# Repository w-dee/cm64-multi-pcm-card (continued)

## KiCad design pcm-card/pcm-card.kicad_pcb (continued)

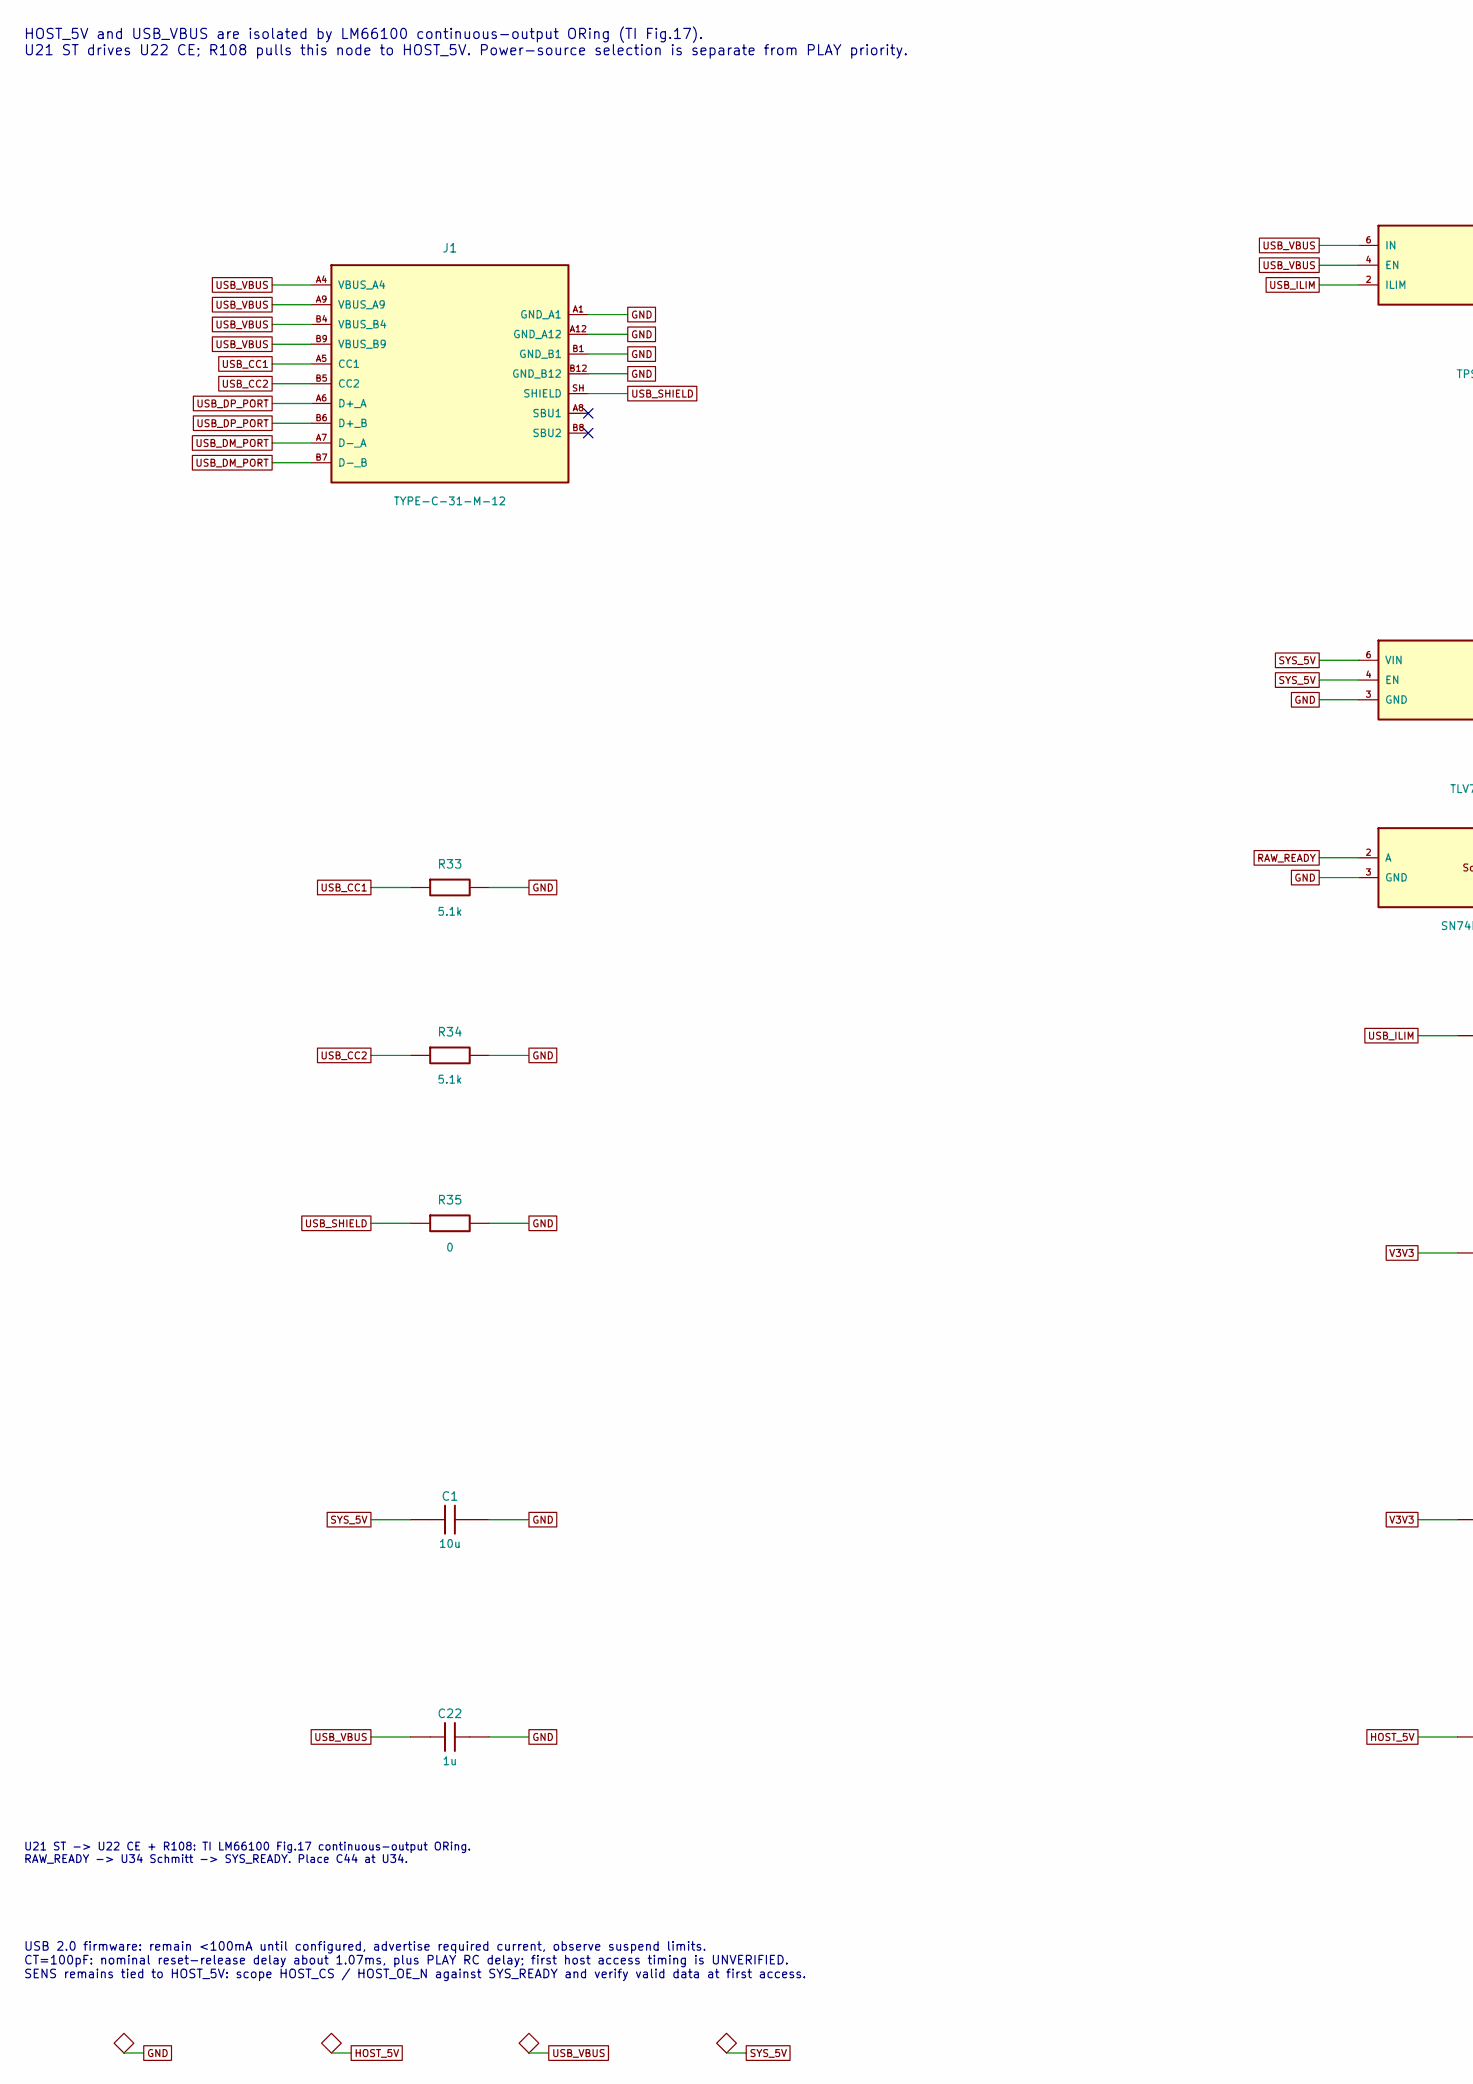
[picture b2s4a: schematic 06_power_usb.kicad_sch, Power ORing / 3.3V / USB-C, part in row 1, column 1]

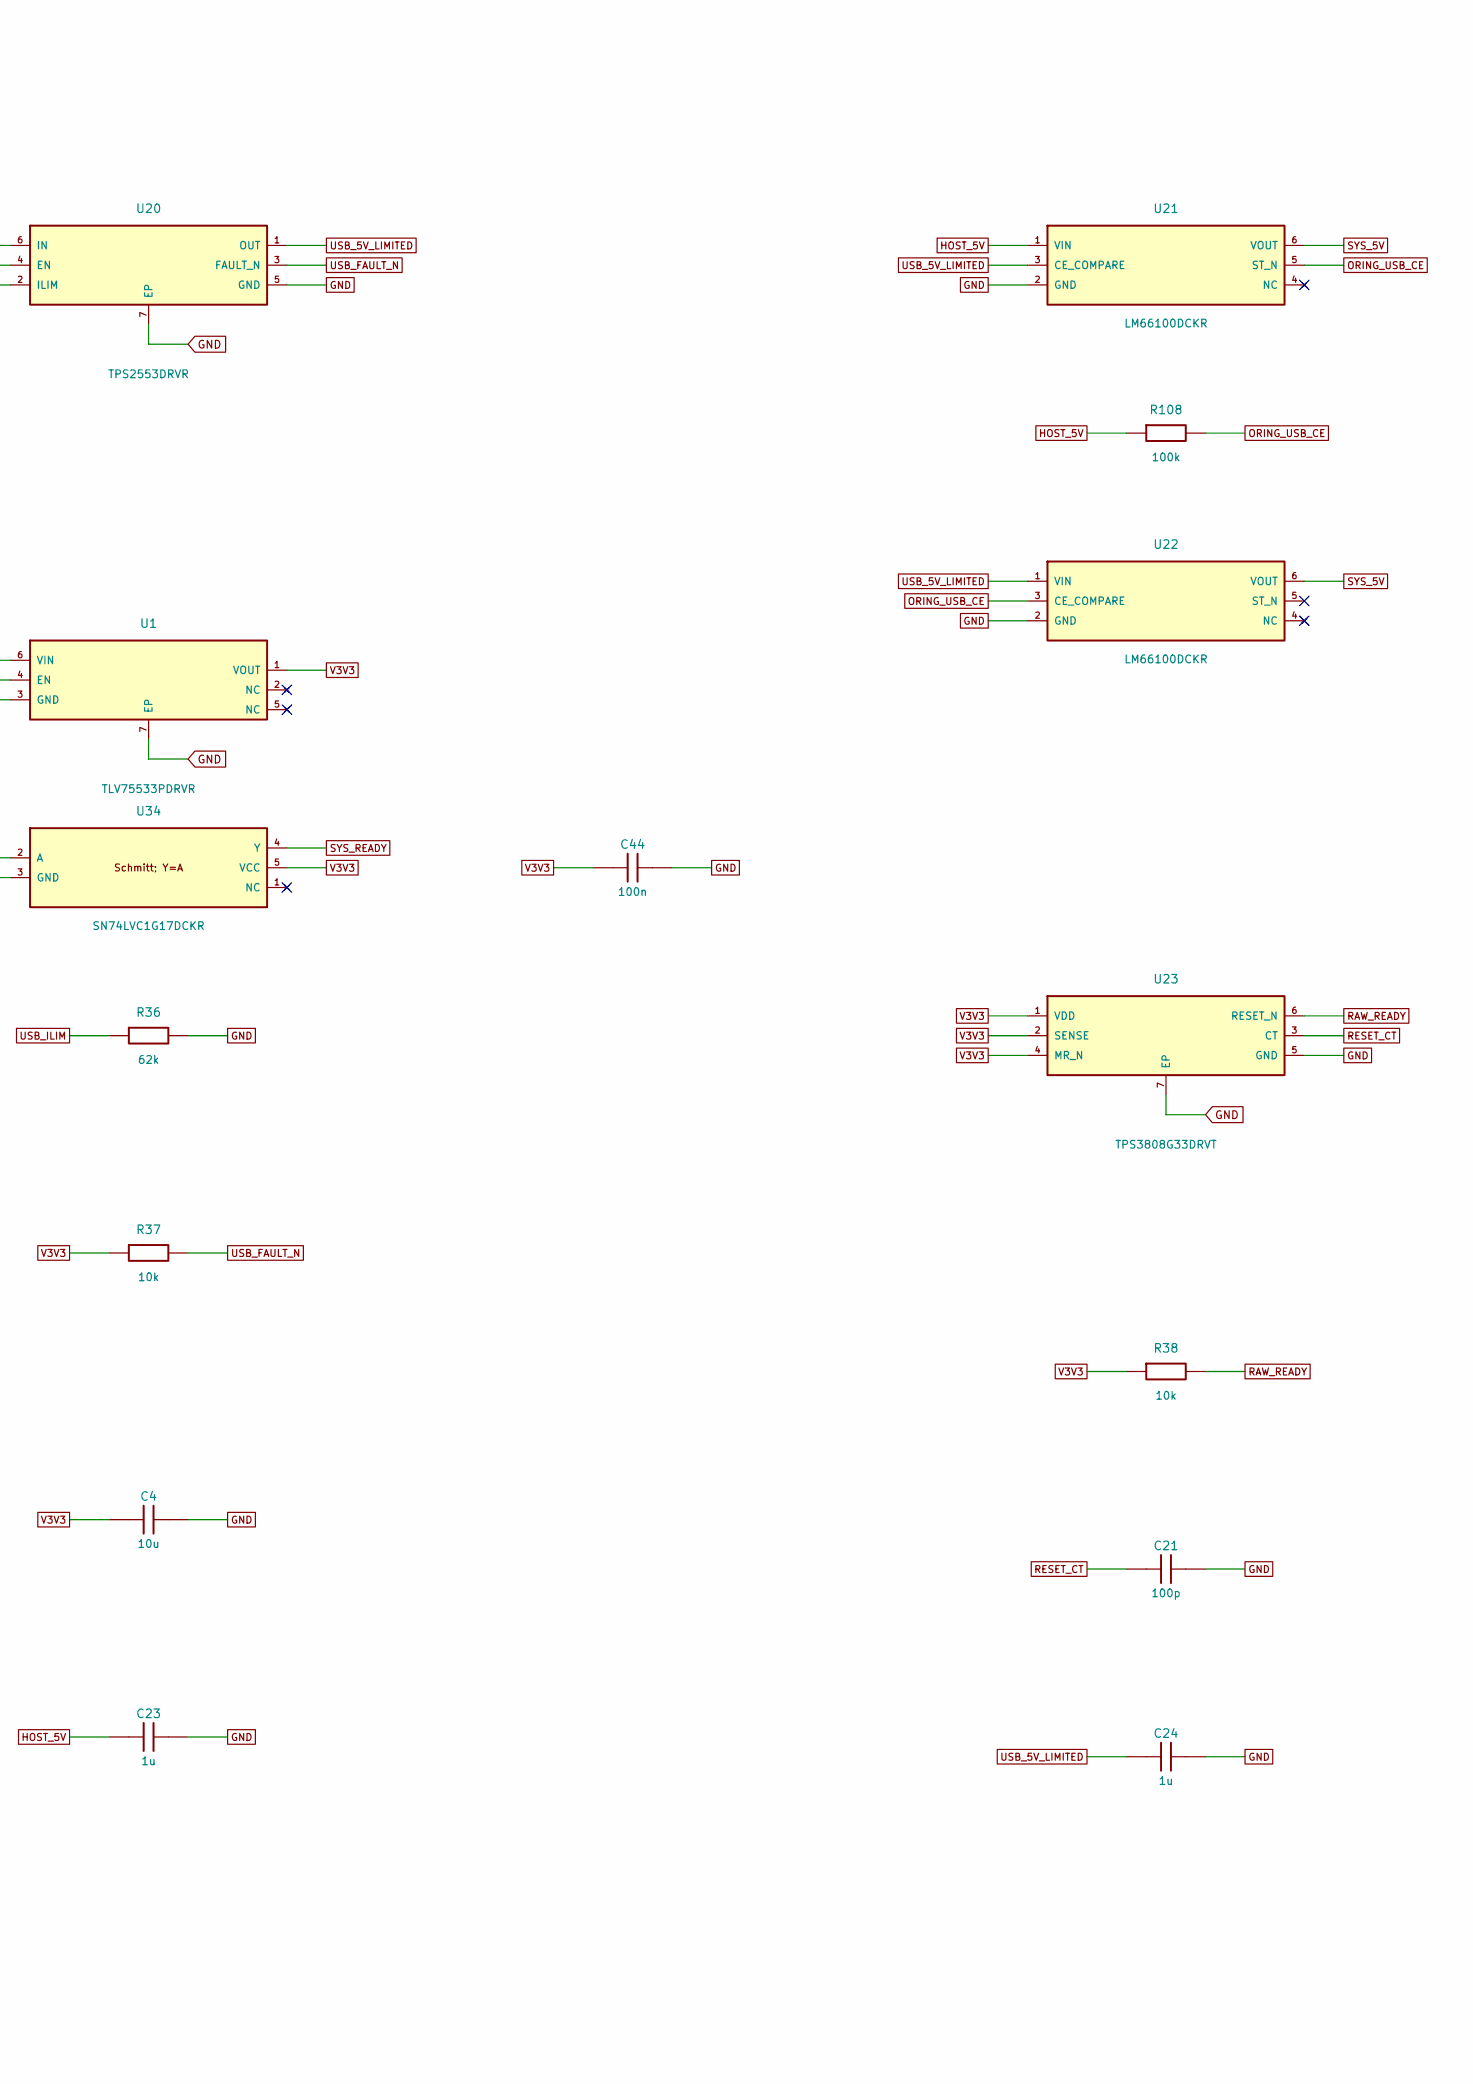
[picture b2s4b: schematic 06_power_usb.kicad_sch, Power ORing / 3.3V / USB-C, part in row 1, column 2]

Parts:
C1, C4: 10u; C_0603_1608Metric; MPN CL10A106KP8NNNC; LCSC C19702
C21: 100p; C_0603_1608Metric; MPN CL10C101JB8NNNC; LCSC C14858
C22, C23, C24: 1u; C_0603_1608Metric; MPN CL10A105KB8NNNC; LCSC C15849
C44: 100n; C_0603_1608Metric; MPN CC0603KRX7R9BB104; LCSC C14663
J1: TYPE-C-31-M-12; USB_C_HRO_TYPE-C-31-M-12; MPN TYPE-C-31-M-12; LCSC C165948
R33, R34: 5.1k; R_0603_1608Metric; MPN 0603WAF5101T5E; LCSC C23186
R35: 0; R_0603_1608Metric; MPN 0603WAF0000T5E; LCSC C21189
R36: 62k; R_0603_1608Metric; MPN 0603WAF6202T5E; LCSC C23221
R37, R38: 10k; R_0603_1608Metric; MPN 0603WAF1002T5E; LCSC C25804
R108: 100k; R_0603_1608Metric; MPN 0603WAF1003T5E; LCSC C25803
U1: TLV75533PDRVR; TI_WSON-6-1EP_2x2mm_P0.65mm_EP1x1.6mm; MPN TLV75533PDRVR; LCSC C2861750
U20: TPS2553DRVR; TI_WSON-6-1EP_2x2mm_P0.65mm_EP1x1.6mm; MPN TPS2553DRVR; LCSC C138719
U21, U22: LM66100DCKR; SC70-6; MPN LM66100DCKR; LCSC C2869734
U23: TPS3808G33DRVT; TI_WSON-6-1EP_2x2mm_P0.65mm_EP1x1.6mm; MPN TPS3808G33DRVT; LCSC C702176
U34: SN74LVC1G17DCKR; SC70-5; MPN SN74LVC1G17DCKR; LCSC C10425

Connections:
GND: C1.2, C4.2, C21.2, C22.2, C23.2, C24.2, C44.2, J1.A1 (GND_A1), J1.A12 (GND_A12), J1.B1 (GND_B1), J1.B12 (GND_B12), R33.2, R34.2, R35.2, R36.2, U1.3 (GND), U1.7 (EP), U20.5 (GND), U20.7 (EP), U21.2 (GND), U22.2 (GND), U23.5 (GND), U23.7 (EP), U34.3 (GND); also elsewhere on the board
HOST_5V: C23.1, R108.1, U21.1 (VIN); also elsewhere on the board
ORING_USB_CE: R108.2, U21.5 (ST_N), U22.3 (CE_COMPARE)
RAW_READY: R38.2, U23.6 (RESET_N), U34.2 (A)
RESET_CT: C21.1, U23.3 (CT)
SYS_5V: C1.1, U1.4 (EN), U1.6 (VIN), U21.6 (VOUT), U22.6 (VOUT); also elsewhere on the board
SYS_READY: U34.4 (Y); also elsewhere on the board
USB_5V_LIMITED: C24.1, U20.1 (OUT), U21.3 (CE_COMPARE), U22.1 (VIN)
USB_CC1: J1.A5 (CC1), R33.1; also elsewhere on the board
USB_CC2: J1.B5 (CC2), R34.1; also elsewhere on the board
USB_DM_PORT: J1.A7 (D-_A), J1.B7 (D-_B); also elsewhere on the board
USB_DP_PORT: J1.A6 (D+_A), J1.B6 (D+_B); also elsewhere on the board
USB_FAULT_N: R37.2, U20.3 (FAULT_N); also elsewhere on the board
USB_ILIM: R36.1, U20.2 (ILIM)
USB_SHIELD: J1.SH (SHIELD), R35.1
USB_VBUS: C22.1, J1.A4 (VBUS_A4), J1.A9 (VBUS_A9), J1.B4 (VBUS_B4), J1.B9 (VBUS_B9), U20.4 (EN), U20.6 (IN); also elsewhere on the board
V3V3: C4.1, C44.1, R37.1, R38.1, U1.1 (VOUT), U23.1 (VDD), U23.2 (SENSE), U23.4 (MR_N), U34.5 (VCC); also elsewhere on the board

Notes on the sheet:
HOST_5V and USB_VBUS are isolated by LM66100 continuous-output ORing (TI Fig.17). U21 ST drives U22 CE; R108 pulls this node to HOST_5V. Power-source selection is separate from PLAY priority.
USB 2.0 firmware: remain <100mA until configured, advertise required current, observe suspend limits. CT=100pF: nominal reset-release delay about 1.07ms, plus PLAY RC delay; first host access timing is UNVERIFIED. SENS remains tied to HOST_5V: scope HOST_CS / HOST_OE_N against SYS_READY and verify 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
U21 ST -> U22 CE + R108: TI LM66100 Fig.17 continuous-output ORing. RAW_READY -> U34 Schmitt -> SYS_READY. Place C44 at U34.

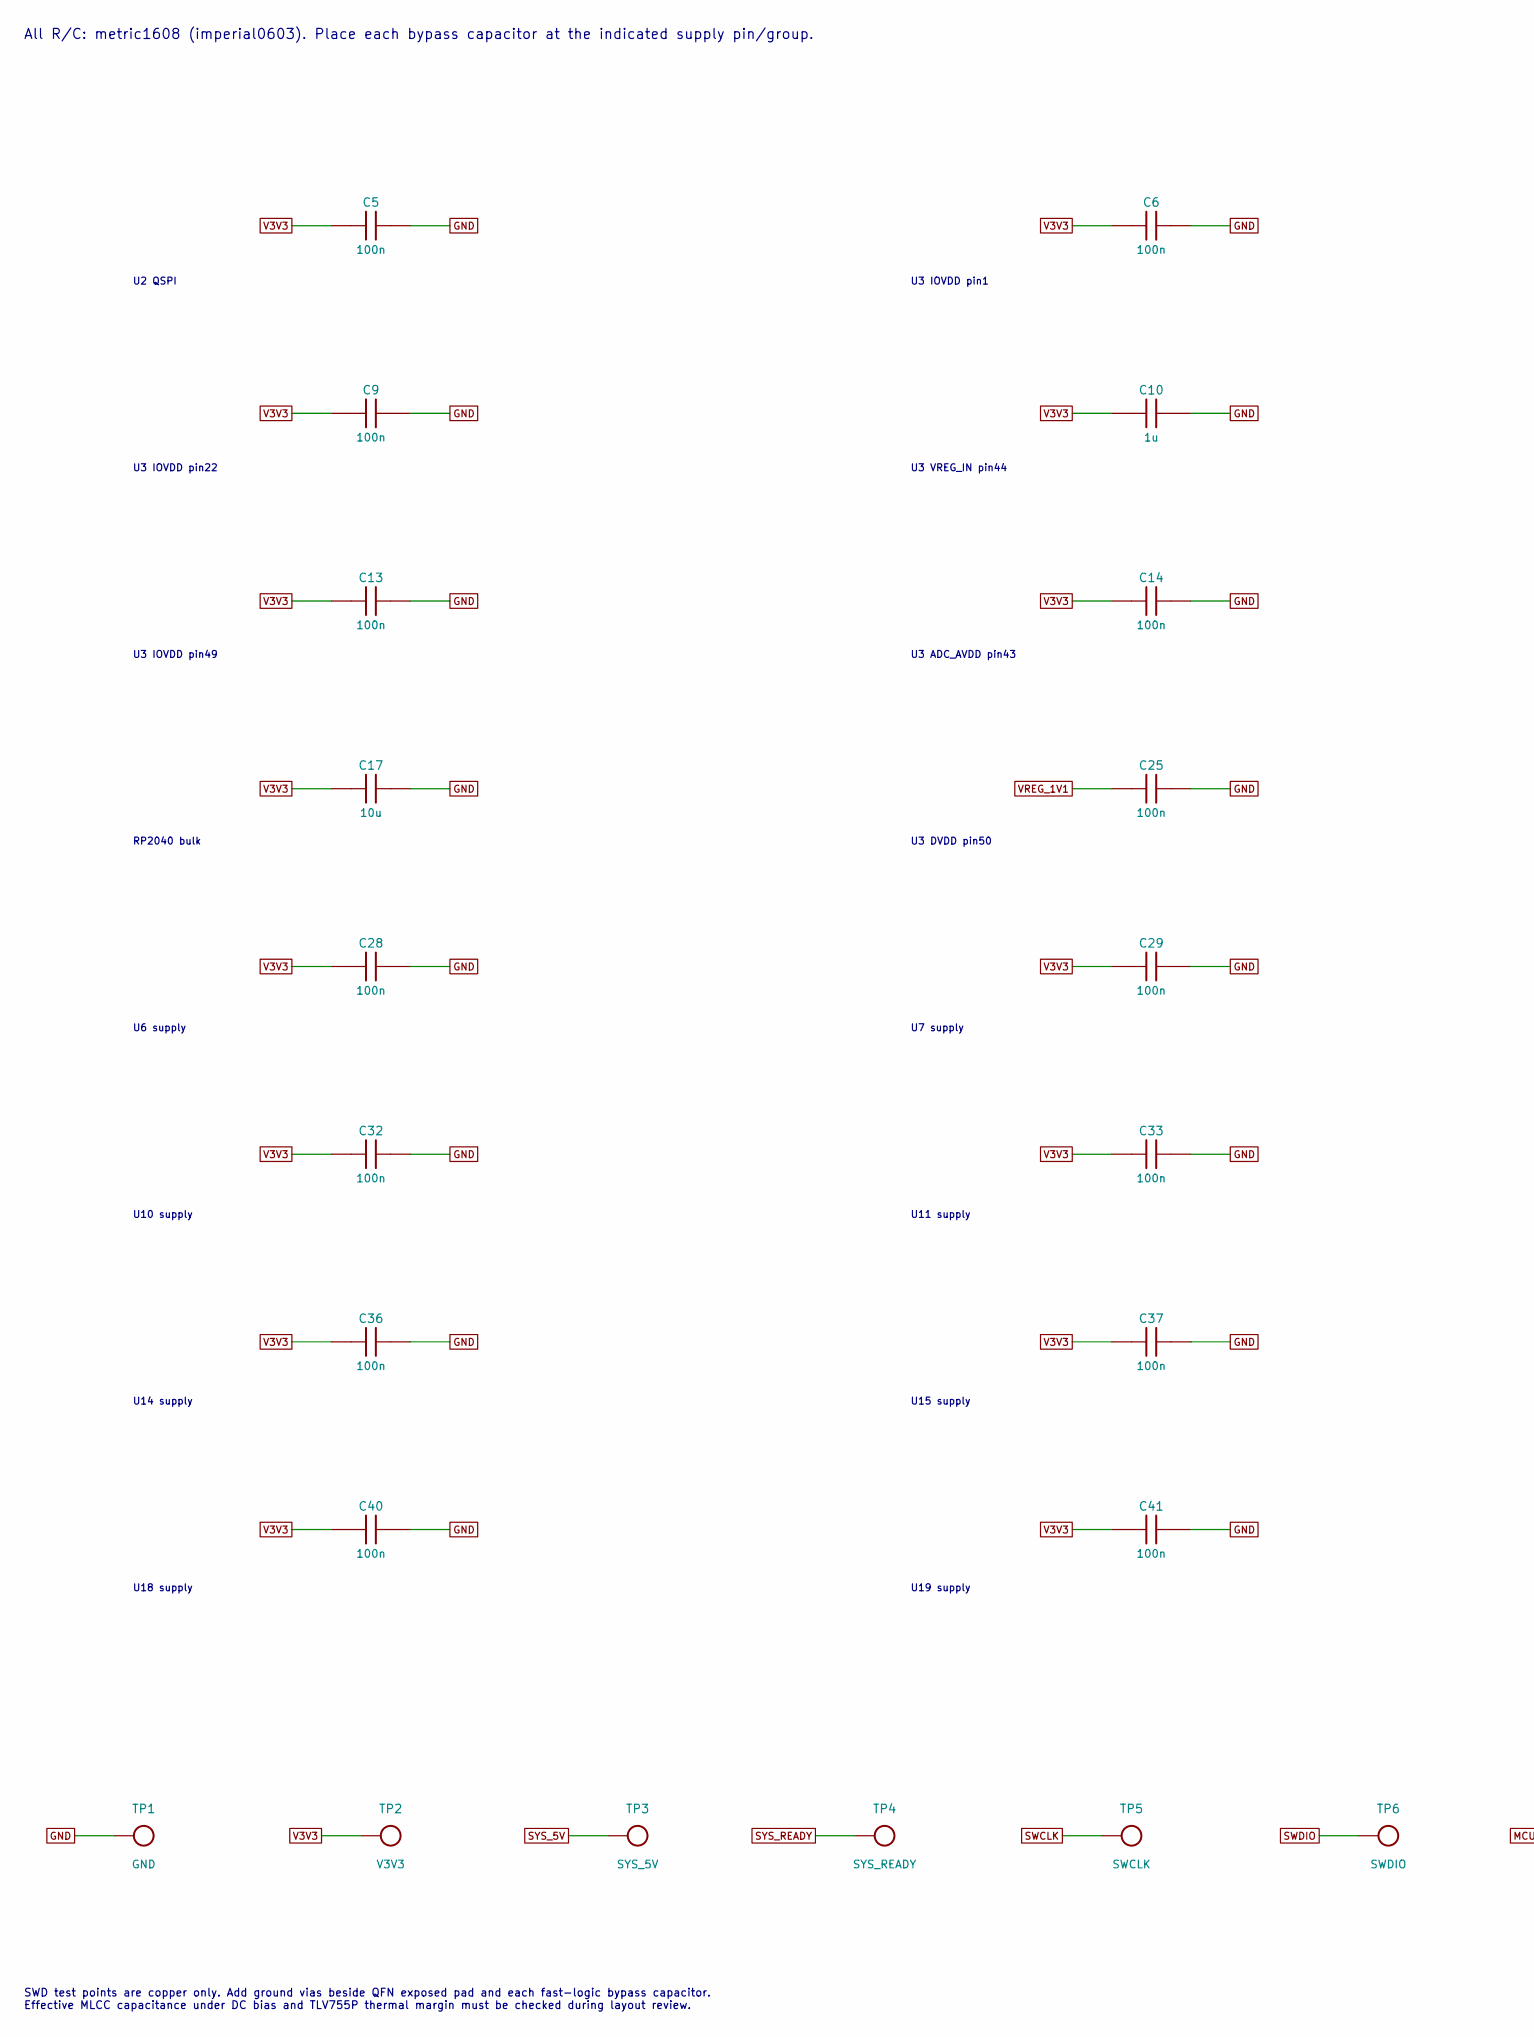
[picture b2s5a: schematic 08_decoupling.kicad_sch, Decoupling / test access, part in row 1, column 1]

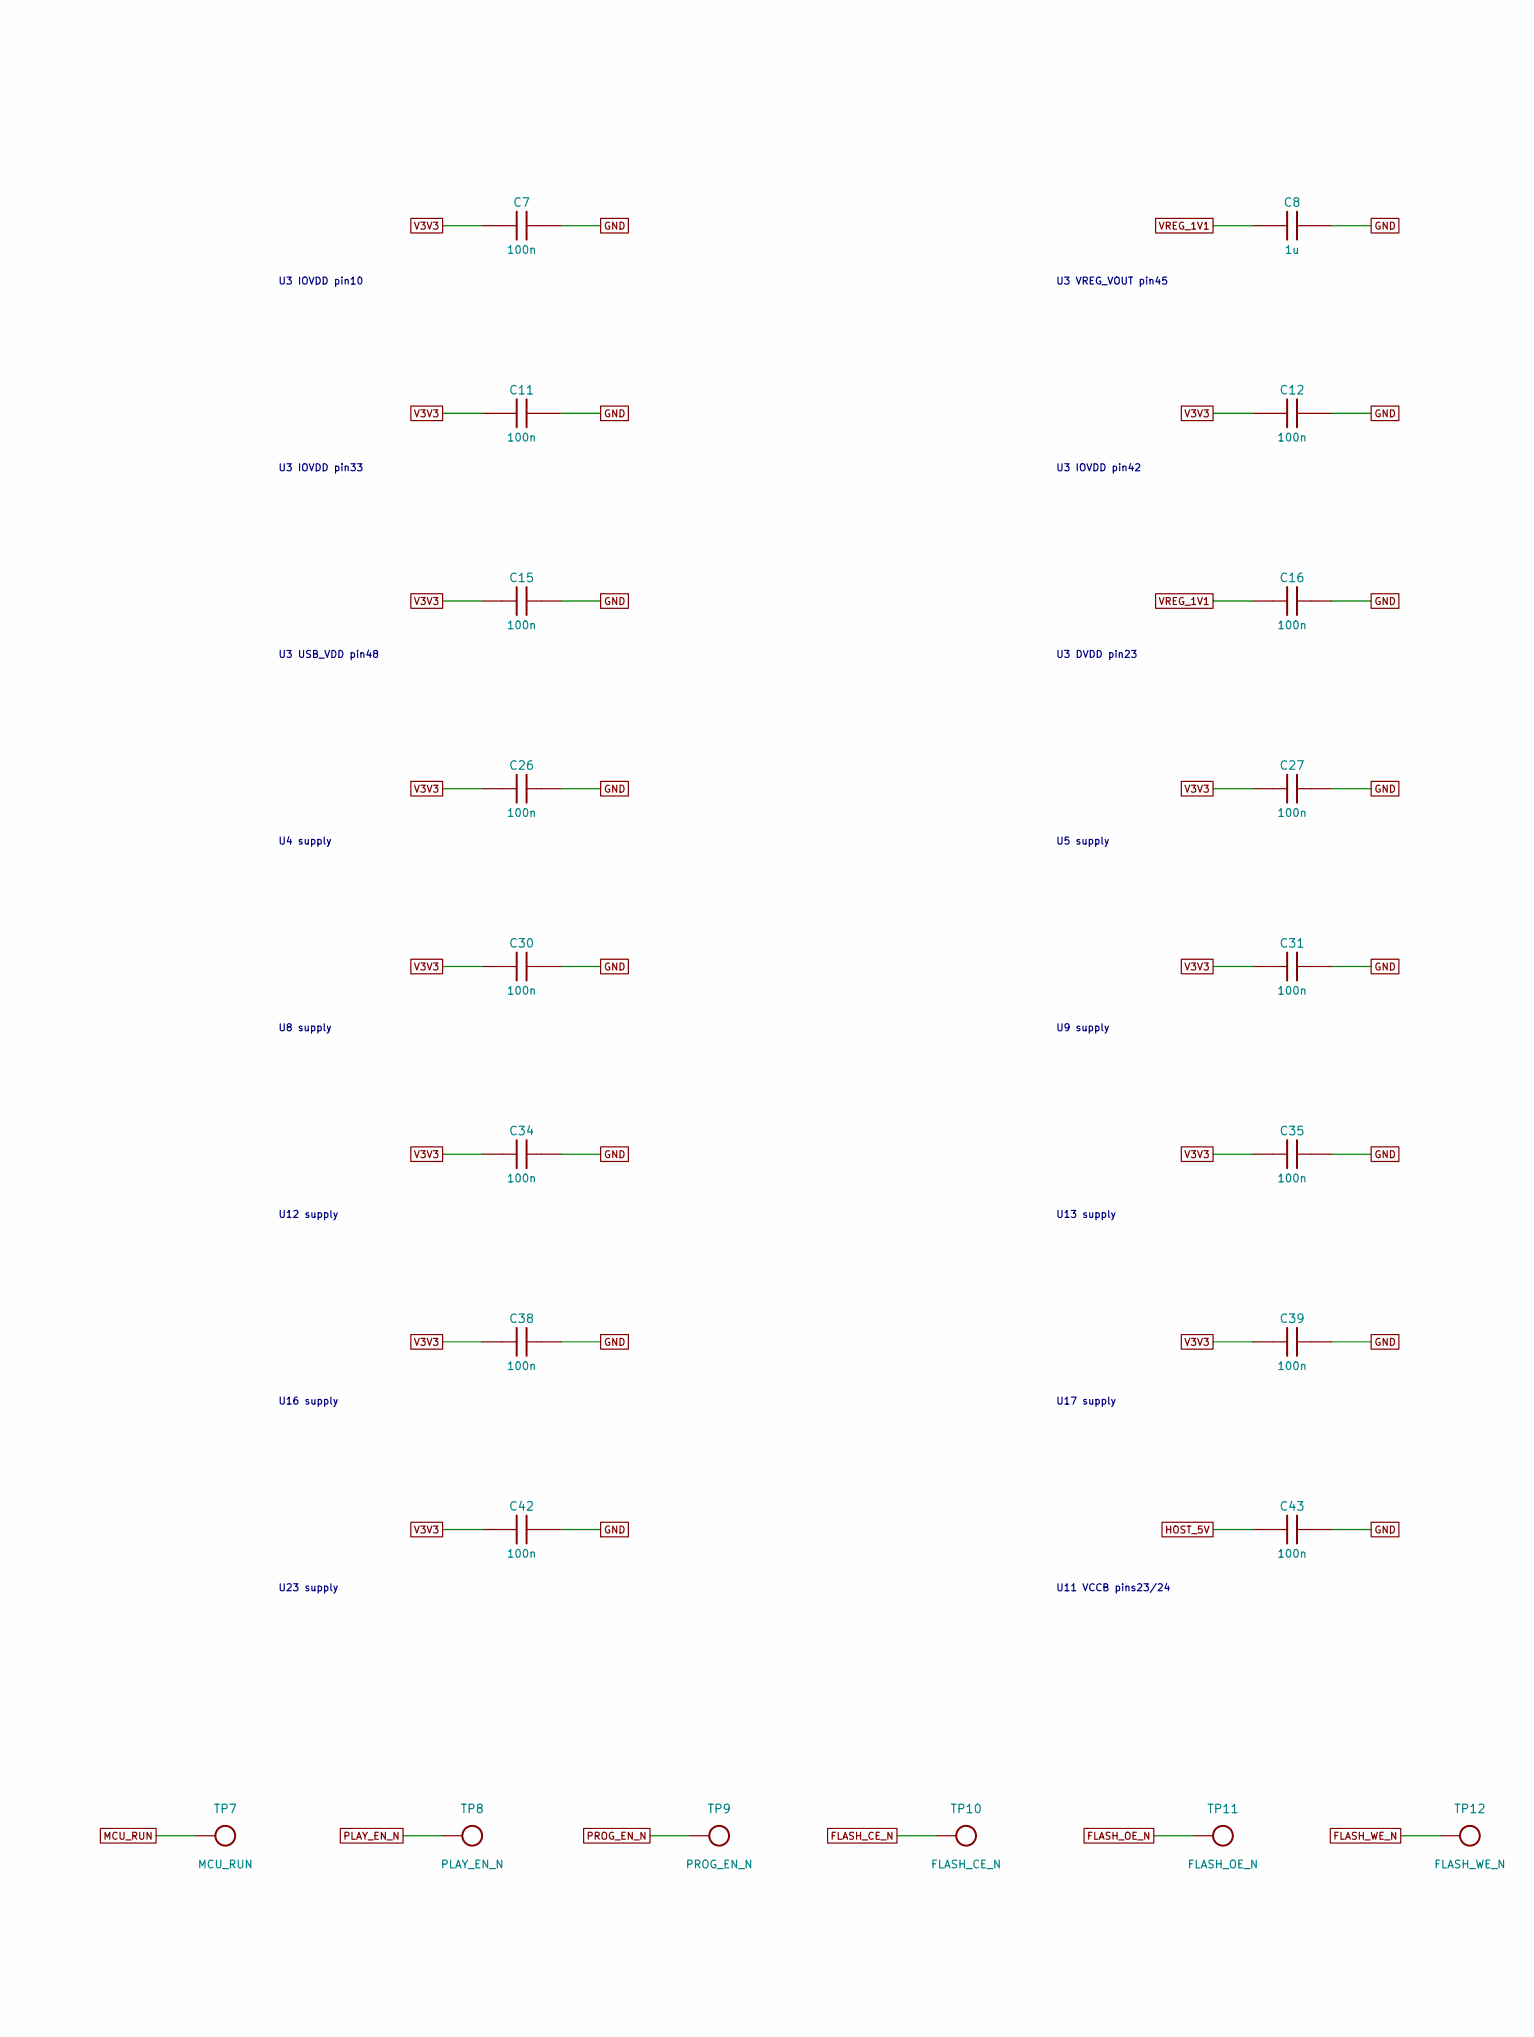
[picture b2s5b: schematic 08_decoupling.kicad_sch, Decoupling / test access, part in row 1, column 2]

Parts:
C5, C6, C7, C9, C11, C12, C13, C14, C15, C16, C25, C26, C27, C28, C29, C30, C31, C32, C33, C34, C35, C36, C37, C38, C39, C40, C41, C42, C43: 100n; C_0603_1608Metric; MPN CC0603KRX7R9BB104; LCSC C14663
C8, C10: 1u; C_0603_1608Metric; MPN CL10A105KB8NNNC; LCSC C15849
C17: 10u; C_0603_1608Metric; MPN CL10A106KP8NNNC; LCSC C19702
TP1: GND; TestPoint_1mm; MPN TestPoint
TP2: V3V3; TestPoint_1mm; MPN TestPoint
TP3: SYS_5V; TestPoint_1mm; MPN TestPoint
TP4: SYS_READY; TestPoint_1mm; MPN TestPoint
TP5: SWCLK; TestPoint_1mm; MPN TestPoint
TP6: SWDIO; TestPoint_1mm; MPN TestPoint
TP7: MCU_RUN; TestPoint_1mm; MPN TestPoint
TP8: PLAY_EN_N; TestPoint_1mm; MPN TestPoint
TP9: PROG_EN_N; TestPoint_1mm; MPN TestPoint
TP10: FLASH_CE_N; TestPoint_1mm; MPN TestPoint
TP11: FLASH_OE_N; TestPoint_1mm; MPN TestPoint
TP12: FLASH_WE_N; TestPoint_1mm; MPN TestPoint

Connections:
FLASH_CE_N: TP10.1; also elsewhere on the board
FLASH_OE_N: TP11.1; also elsewhere on the board
FLASH_WE_N: TP12.1; also elsewhere on the board
GND: C5.2, C6.2, C7.2, C8.2, C9.2, C10.2, C11.2, C12.2, C13.2, C14.2, C15.2, C16.2, C17.2, C25.2, C26.2, C27.2, C28.2, C29.2, C30.2, C31.2, C32.2, C33.2, C34.2, C35.2, C36.2, C37.2, C38.2, C39.2, C40.2, C41.2, C42.2, C43.2, TP1.1; also elsewhere on the board
HOST_5V: C43.1; also elsewhere on the board
MCU_RUN: TP7.1; also elsewhere on the board
PLAY_EN_N: TP8.1; also elsewhere on the board
PROG_EN_N: TP9.1; also elsewhere on the board
SWCLK: TP5.1; also elsewhere on the board
SWDIO: TP6.1; also elsewhere on the board
SYS_5V: TP3.1; also elsewhere on the board
SYS_READY: TP4.1; also elsewhere on the board
V3V3: C5.1, C6.1, C7.1, C9.1, C10.1, C11.1, C12.1, C13.1, C14.1, C15.1, C17.1, C26.1, C27.1, C28.1, C29.1, C30.1, C31.1, C32.1, C33.1, C34.1, C35.1, C36.1, C37.1, C38.1, C39.1, C40.1, C41.1, C42.1, TP2.1; also elsewhere on the board
VREG_1V1: C8.1, C16.1, C25.1; also elsewhere on the board

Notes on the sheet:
All R/C: metric1608 (imperial0603). Place each bypass capacitor at the indicated supply pin/group.
SWD test points are copper only. Add ground vias beside QFN exposed pad and each fast-logic bypass capacitor. Effective MLCC capacitance under DC bias and TLV755P thermal margin must be checked during layout review.
U19 supply
U15 supply
U12 supply
U3 IOVDD pin42
U5 supply
U10 supply
U3 IOVDD pin10
U6 supply
U17 supply
U3 VREG_IN pin44
U18 supply
U16 supply
U3 DVDD pin23
U7 supply
RP2040 bulk
U8 supply
U9 supply
U11 supply
U3 IOVDD pin49
U3 VREG_VOUT pin45
U4 supply
U23 supply
U3 IOVDD pin1
U2 QSPI
U13 supply
U3 IOVDD pin22
U3 ADC_AVDD pin43
U3 DVDD pin50
U3 IOVDD pin33
U14 supply
U3 USB_VDD pin48
U11 VCCB pins23/24

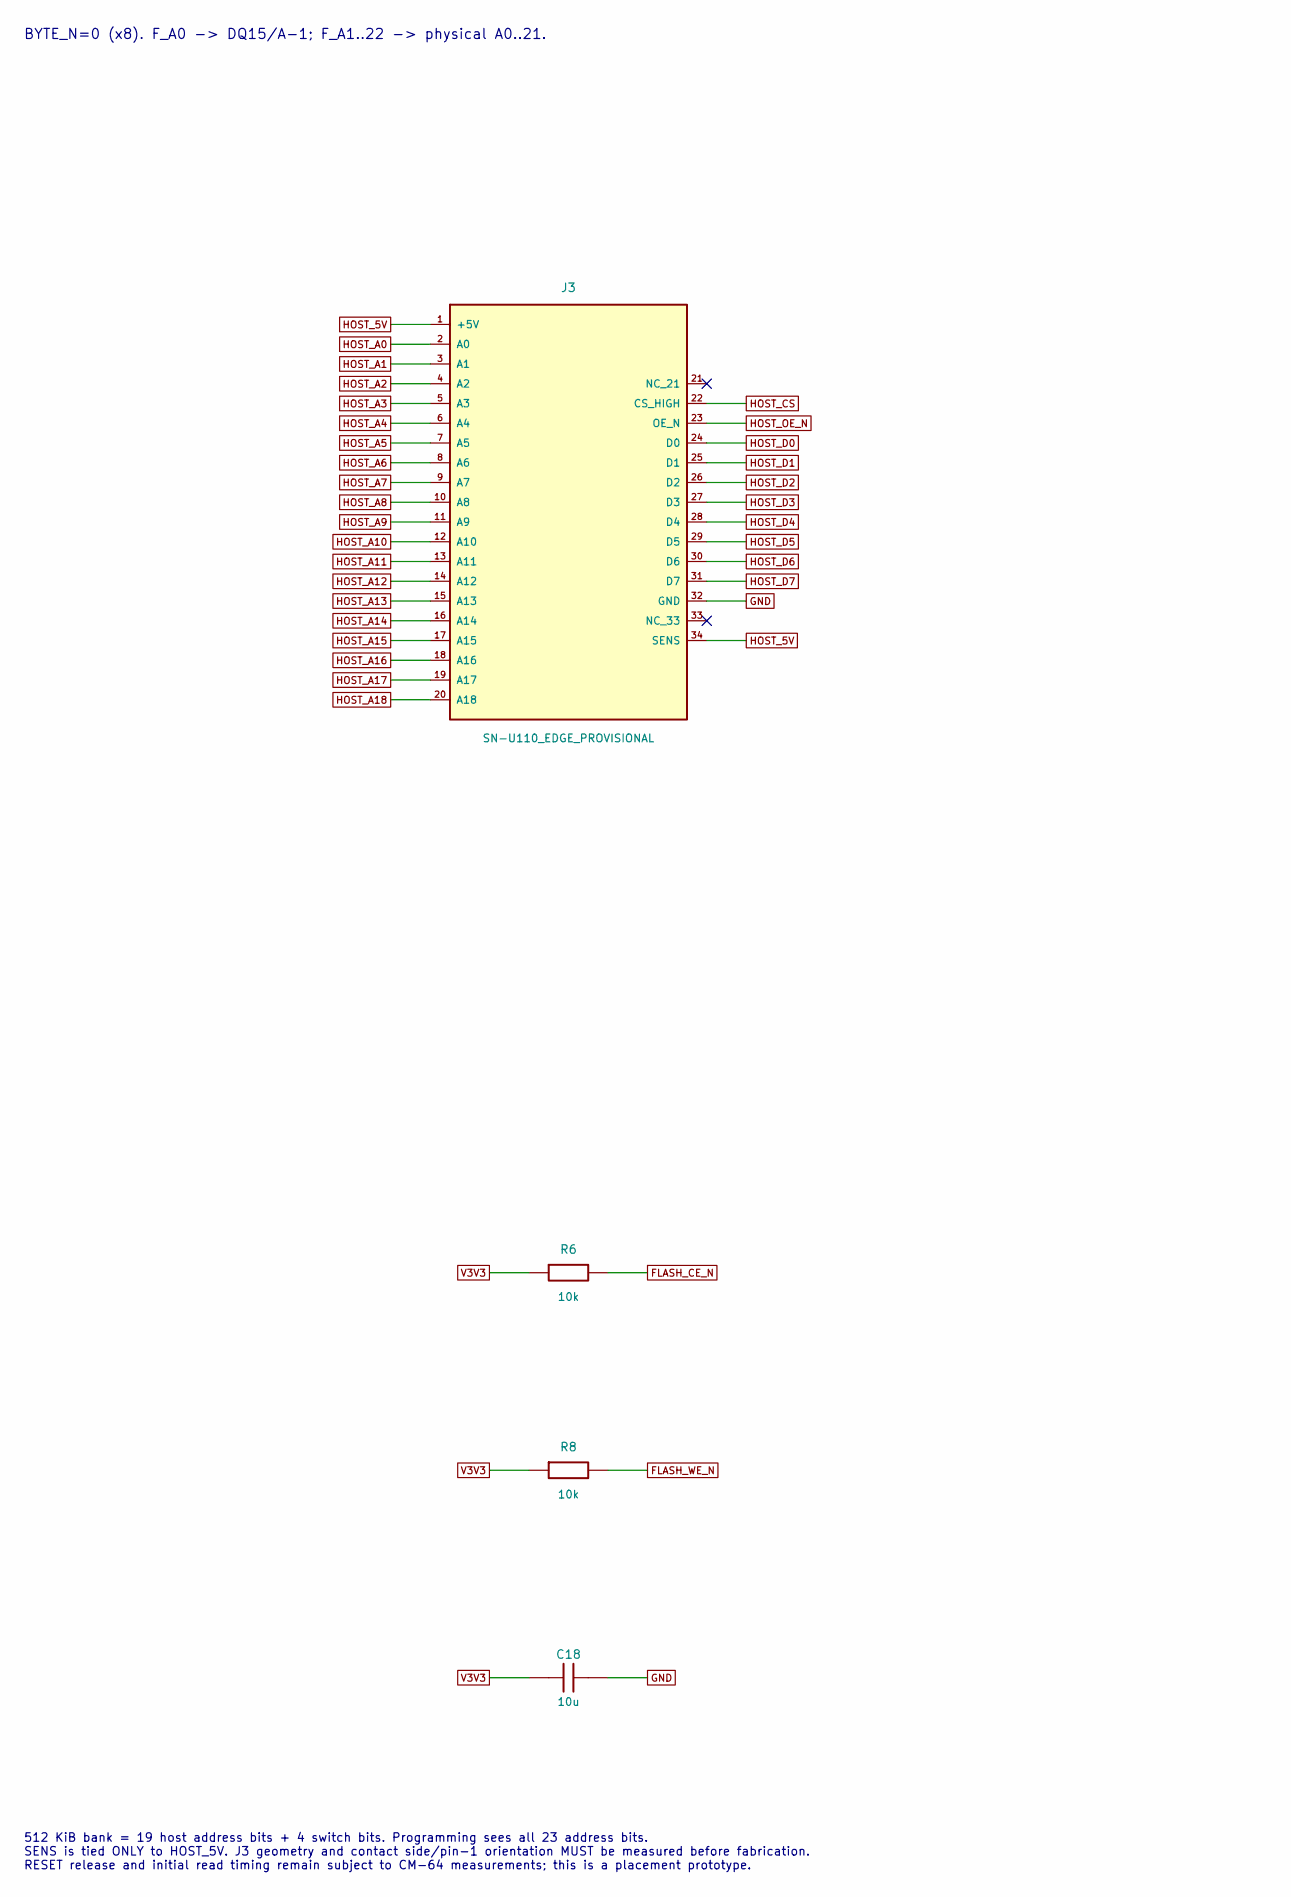
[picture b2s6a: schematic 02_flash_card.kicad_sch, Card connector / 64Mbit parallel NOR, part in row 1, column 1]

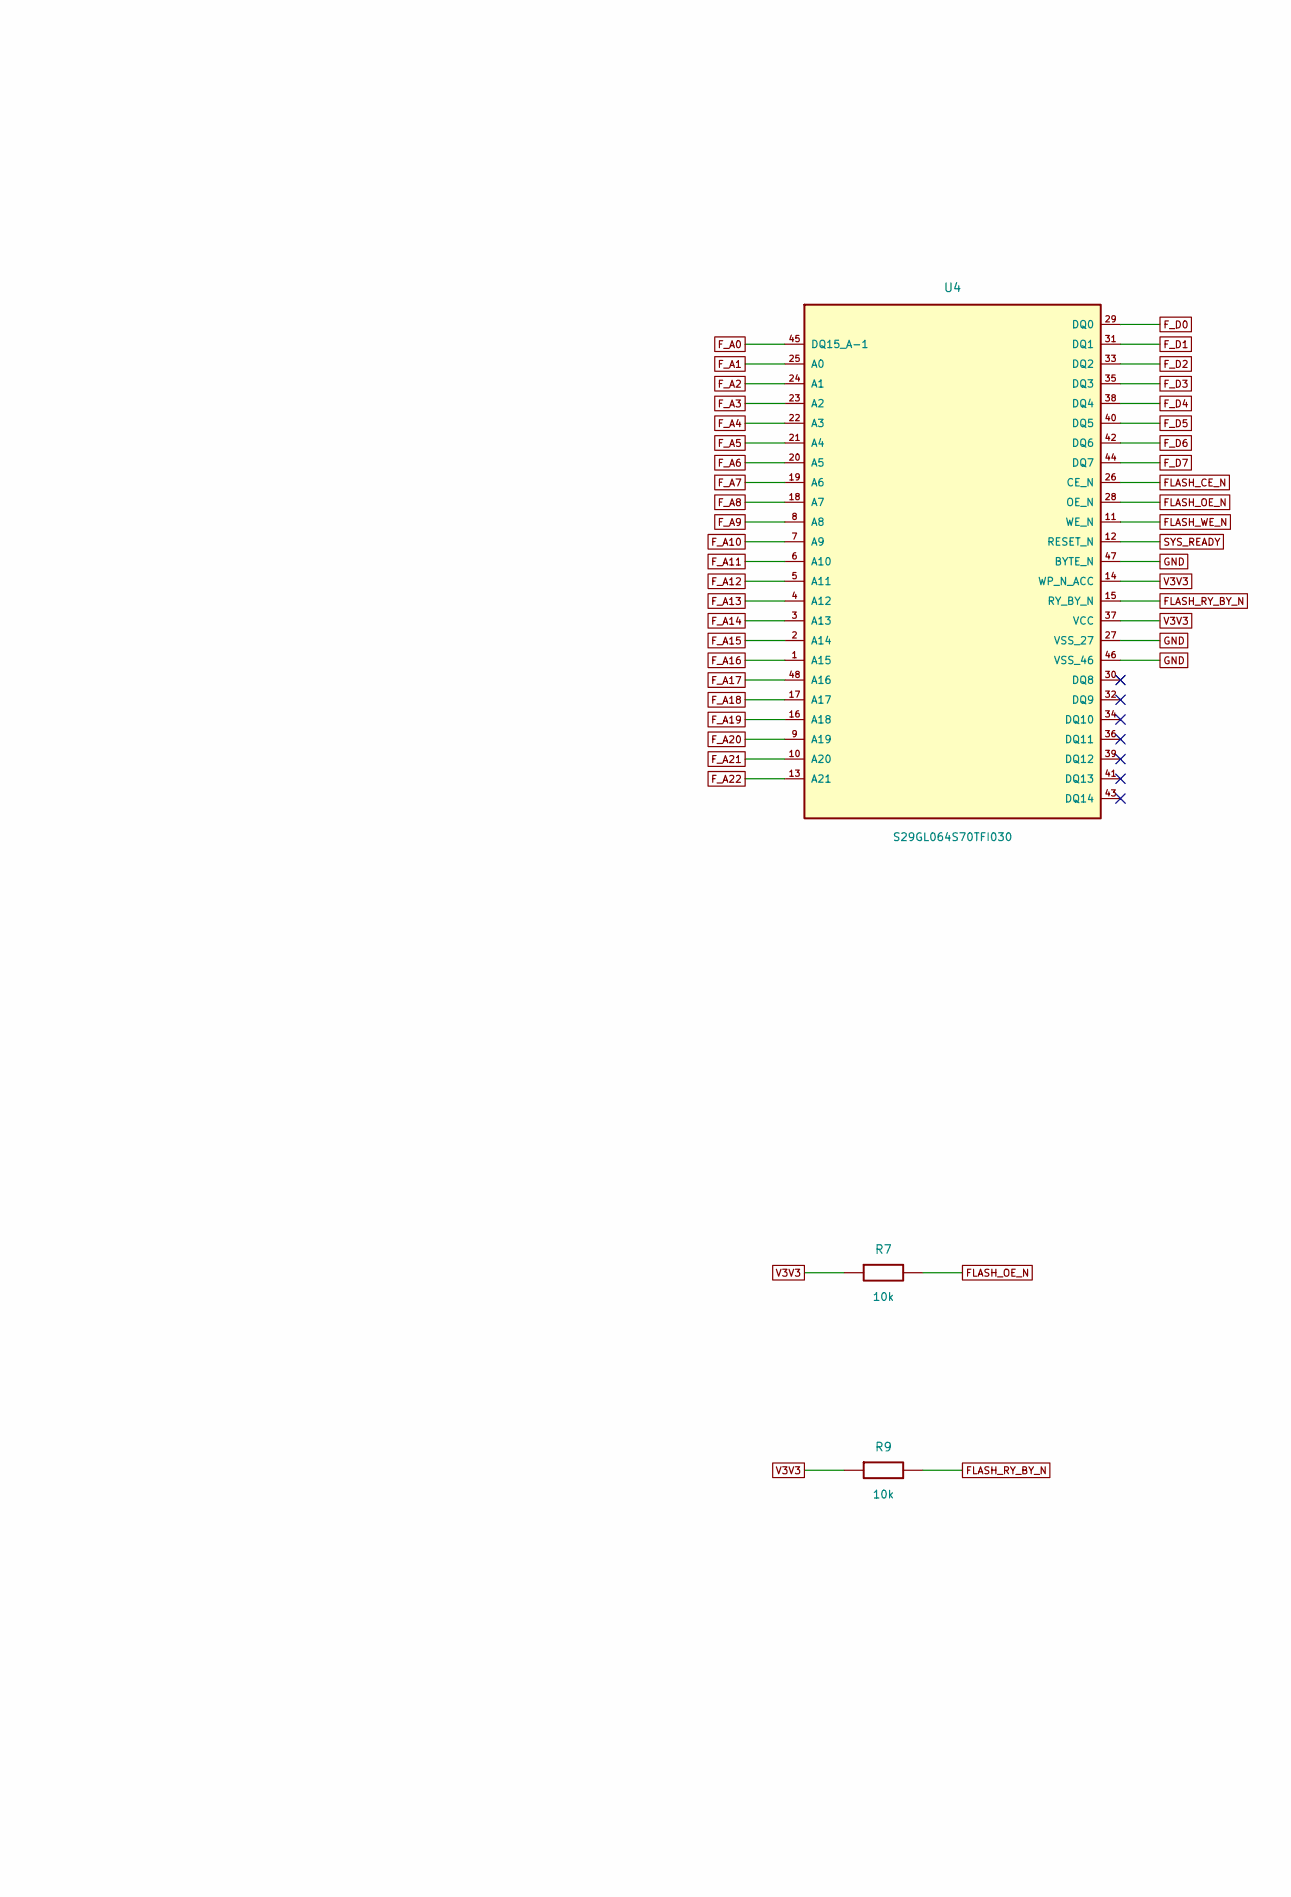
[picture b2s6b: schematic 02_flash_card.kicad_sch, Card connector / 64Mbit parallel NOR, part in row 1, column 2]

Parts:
C18: 10u; C_0603_1608Metric; MPN CL10A106KP8NNNC; LCSC C19702
J3: SN-U110_EDGE_PROVISIONAL; CardEdge_34_P1.50_PROVISIONAL; MPN SN-U110_EDGE_PROVISIONAL
R6, R7, R8, R9: 10k; R_0603_1608Metric; MPN 0603WAF1002T5E; LCSC C25804
U4: S29GL064S70TFI030; TSOP-I-48_18.4x12_P0.5; MPN S29GL064S70TFI030; LCSC C2944625

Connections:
FLASH_CE_N: R6.2, U4.26 (CE_N); also elsewhere on the board
FLASH_OE_N: R7.2, U4.28 (OE_N); also elsewhere on the board
FLASH_RY_BY_N: R9.2, U4.15 (RY_BY_N); also elsewhere on the board
FLASH_WE_N: R8.2, U4.11 (WE_N); also elsewhere on the board
F_A0: U4.45 (DQ15_A-1); also elsewhere on the board
F_A1: U4.25 (A0); also elsewhere on the board
F_A2: U4.24 (A1); also elsewhere on the board
F_A3: U4.23 (A2); also elsewhere on the board
F_A4: U4.22 (A3); also elsewhere on the board
F_A5: U4.21 (A4); also elsewhere on the board
F_A6: U4.20 (A5); also elsewhere on the board
F_A7: U4.19 (A6); also elsewhere on the board
F_A8: U4.18 (A7); also elsewhere on the board
F_A9: U4.8 (A8); also elsewhere on the board
F_A10: U4.7 (A9); also elsewhere on the board
F_A11: U4.6 (A10); also elsewhere on the board
F_A12: U4.5 (A11); also elsewhere on the board
F_A13: U4.4 (A12); also elsewhere on the board
F_A14: U4.3 (A13); also elsewhere on the board
F_A15: U4.2 (A14); also elsewhere on the board
F_A16: U4.1 (A15); also elsewhere on the board
F_A17: U4.48 (A16); also elsewhere on the board
F_A18: U4.17 (A17); also elsewhere on the board
F_A19: U4.16 (A18); also elsewhere on the board
F_A20: U4.9 (A19); also elsewhere on the board
F_A21: U4.10 (A20); also elsewhere on the board
F_A22: U4.13 (A21); also elsewhere on the board
F_D0: U4.29 (DQ0); also elsewhere on the board
F_D1: U4.31 (DQ1); also elsewhere on the board
F_D2: U4.33 (DQ2); also elsewhere on the board
F_D3: U4.35 (DQ3); also elsewhere on the board
F_D4: U4.38 (DQ4); also elsewhere on the board
F_D5: U4.40 (DQ5); also elsewhere on the board
F_D6: U4.42 (DQ6); also elsewhere on the board
F_D7: U4.44 (DQ7); also elsewhere on the board
GND: C18.2, J3.32 (GND), U4.27 (VSS_27), U4.46 (VSS_46), U4.47 (BYTE_N); also elsewhere on the board
HOST_5V: J3.1 (+5V), J3.34 (SENS); also elsewhere on the board
HOST_A0: J3.2 (A0); also elsewhere on the board
HOST_A1: J3.3 (A1); also elsewhere on the board
HOST_A2: J3.4 (A2); also elsewhere on the board
HOST_A3: J3.5 (A3); also elsewhere on the board
HOST_A4: J3.6 (A4); also elsewhere on the board
HOST_A5: J3.7 (A5); also elsewhere on the board
HOST_A6: J3.8 (A6); also elsewhere on the board
HOST_A7: J3.9 (A7); also elsewhere on the board
HOST_A8: J3.10 (A8); also elsewhere on the board
HOST_A9: J3.11 (A9); also elsewhere on the board
HOST_A10: J3.12 (A10); also elsewhere on the board
HOST_A11: J3.13 (A11); also elsewhere on the board
HOST_A12: J3.14 (A12); also elsewhere on the board
HOST_A13: J3.15 (A13); also elsewhere on the board
HOST_A14: J3.16 (A14); also elsewhere on the board
HOST_A15: J3.17 (A15); also elsewhere on the board
HOST_A16: J3.18 (A16); also elsewhere on the board
HOST_A17: J3.19 (A17); also elsewhere on the board
HOST_A18: J3.20 (A18); also elsewhere on the board
HOST_CS: J3.22 (CS_HIGH); also elsewhere on the board
HOST_D0: J3.24 (D0); also elsewhere on the board
HOST_D1: J3.25 (D1); also elsewhere on the board
HOST_D2: J3.26 (D2); also elsewhere on the board
HOST_D3: J3.27 (D3); also elsewhere on the board
HOST_D4: J3.28 (D4); also elsewhere on the board
HOST_D5: J3.29 (D5); also elsewhere on the board
HOST_D6: J3.30 (D6); also elsewhere on the board
HOST_D7: J3.31 (D7); also elsewhere on the board
HOST_OE_N: J3.23 (OE_N); also elsewhere on the board
SYS_READY: U4.12 (RESET_N); also elsewhere on the board
V3V3: C18.1, R6.1, R7.1, R8.1, R9.1, U4.14 (WP_N_ACC), U4.37 (VCC); also elsewhere on the board

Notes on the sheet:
BYTE_N=0 (x8). F_A0 -> DQ15/A-1; F_A1..22 -> physical A0..21.
512 KiB bank = 19 host address bits + 4 switch bits. Programming sees all 23 address bits. SENS is tied ONLY to HOST_5V. J3 geometry and contact side/pin-1 orientation MUST be measured before fabrication. RESET release and initial read timing remain subject to CM-64 measurements; this is a placemen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
